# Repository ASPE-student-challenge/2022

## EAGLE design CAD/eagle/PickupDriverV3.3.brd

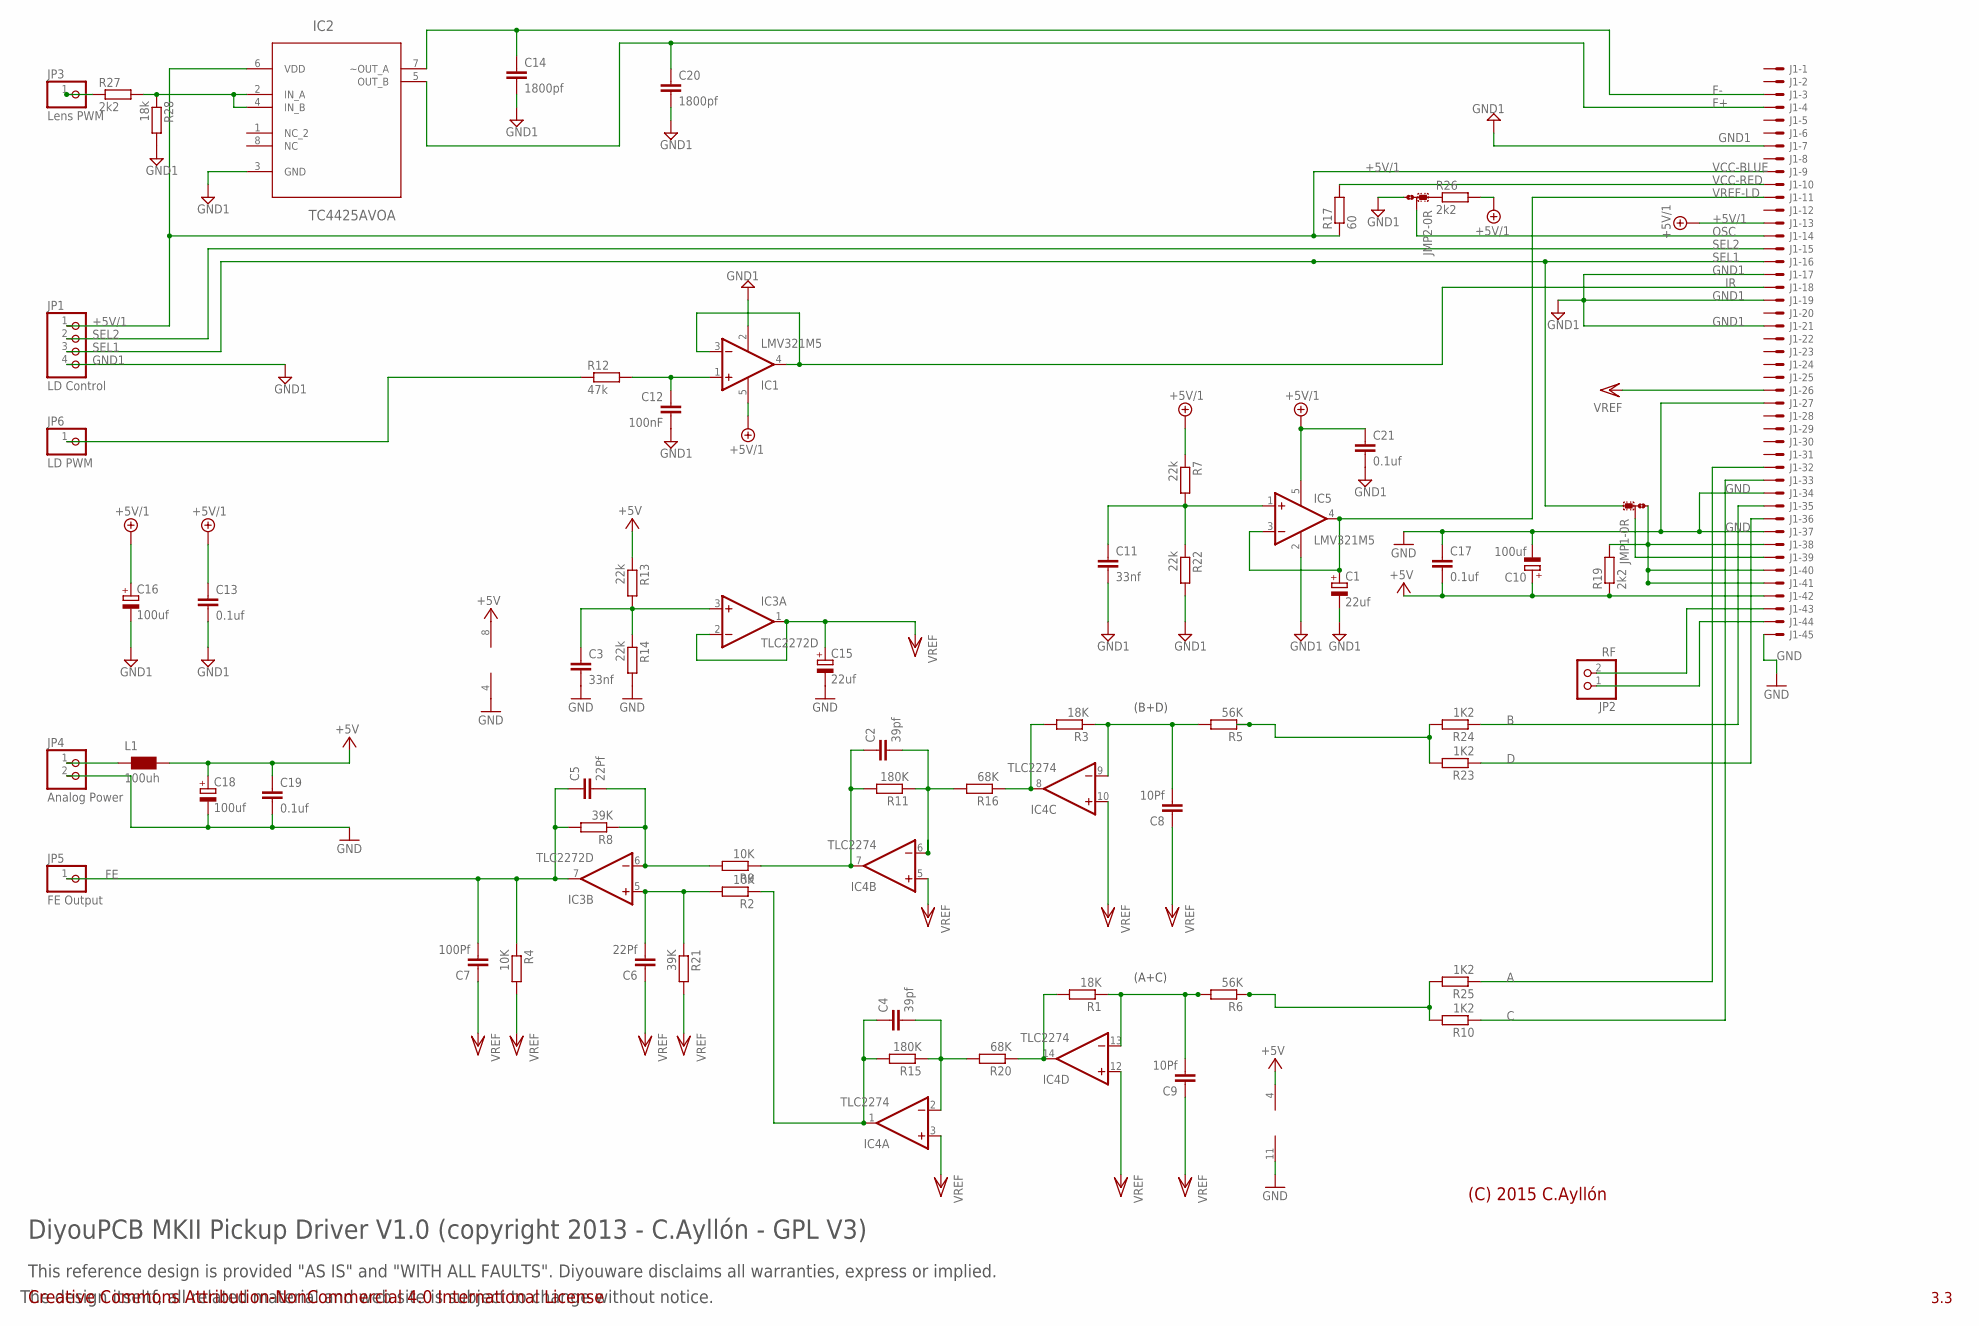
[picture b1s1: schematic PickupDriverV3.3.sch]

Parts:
C1, C15: 22uf; SMC_C
C2, C4: 39pf; C1206K
C3, C11: 33nf; C1206K
C5, C6: 22Pf; C1206K
C7: 100Pf; C1206K
C8, C9: 10Pf; C1206K
C10, C16, C18: 100uf; SMC_C
C12: 100nF; C1206K
C13, C17, C19, C21: 0.1uf; C1206K
C14, C20: 1800pf; C1206K
IC1, IC5: LMV321M5; SOT23-5
IC2: TC4425AVOA; SOIC127P600X175-8N
IC3: TLC2272D; SO08
IC4: TLC2274; SO14
J1: XF2H-4515-1LW
JMP1, JMP2: 0R-JUMPA; A0R-JMP
JP1: LD Control; 1X04
JP2: RF; 1X02
JP3: Lens PWM; 1X01
JP4: Analog Power; 1X02
JP5: FE Output; 1X01
JP6: LD PWM; 1X01
L1: 100uh; CHOKE-100UH-1
R1, R3: 18K; R1206
R2, R4, R9: 10K; R1206
R5, R6: 56K; R1206
R7, R13, R14, R22: 22k; R1206
R8, R21: 39K; R1206
R10, R23, R24, R25: 1K2; R1206
R11, R15: 180K; R1206
R12: 47k; R1206
R16, R20: 68K; R1206
R17: 60; R1206
R19, R26, R27: 2k2; R1206
R28: 18k; R1206

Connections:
+5V: C10.+, C17.2, C18.+, C19.1, IC3.8 (V+), IC4.4 (V+), J1.42 (MS), L1.2, R13.1, R19.1
+5V/1: C13.1, C16.+, C21.1, IC1.5 (V+), IC2.6 (VDD), IC5.5 (V+), J1.9 (MS), J1.13 (MS), JP1.1, R7.1, R17.1, R26.2
A: J1.32 (MS), R25.1
B: J1.35 (MS), R24.1
C: J1.33 (MS), R10.1
D: J1.36 (MS), R23.1
F+: C20.1, IC2.5 (OUT_B), J1.4 (MS)
F-: C14.1, IC2.7 (~OUT_A), J1.3 (MS)
FE: C5.1, C7.2, IC3.7 (OUT), JP5.1, R4.1, R8.2
FOCUS: IC2.2 (IN_A), IC2.4 (IN_B), R27.2, R28.1
GND: C3.2, C10.-, C15.-, C17.1, C18.-, C19.2, IC3.4 (V-), IC4.11 (V-), J1.27 (MS), J1.34 (MS), J1.37 (MS), J1.45 (MS), JP4.2, R14.2
GND1: C1.-, C11.2, C12.2, C13.2, C14.2, C16.-, C20.2, C21.2, IC1.2 (V-), IC2.3 (GND), IC5.2 (V-), J1.7 (MS), J1.17 (MS), J1.19 (MS), J1.21 (MS), JMP2.3, JP1.4, R22.2, R28.2
IR: IC1.3 (-IN), IC1.4 (OUT), J1.18 (MS)
LASER_CURR: JP6.1, R12.1
LENS: JP3.1, R27.1
unnamed: C11.1, IC5.1 (+IN), R7.2, R22.1
unnamed: C2.1, IC4.7 (OUT), R9.1, R11.2
unnamed: C12.1, IC1.1 (+IN), R12.2
unnamed: C8.2, IC4.9 (-IN), R3.1, R5.2
unnamed: IC4.14 (OUT), R1.2, R20.1
unnamed: C3.1, IC3.3 (+IN), R13.2, R14.1
unnamed: IC4.8 (OUT), R3.2, R16.1
unnamed: C9.2, IC4.13 (-IN), R1.1, R6.2
unnamed: C2.2, IC4.6 (-IN), R11.1, R16.2
unnamed: C5.2, IC3.6 (-IN), R8.1, R9.2
unnamed: C6.2, IC3.5 (+IN), R2.2, R21.1
unnamed: JP4.1, L1.1
unnamed: JMP2.1, R26.1
unnamed: C4.1, IC4.1 (OUT), R2.1, R15.2
unnamed: C4.2, IC4.2 (-IN), R15.1, R20.2
unnamed: R6.1, R10.2, R25.2
unnamed: J1.43 (MS), JP2.2
unnamed: J1.44 (MS), JP2.1
unnamed: R5.1, R23.2, R24.2
ND: J1.38 (MS), J1.40 (MS), J1.41 (MS), JMP1.3, R19.2
OSC: J1.14 (MS), JMP2.2
REDVCC: J1.10 (MS), R17.2
SEL1: J1.16 (MS), JMP1.1, JP1.3
SEL2: J1.15 (MS), JP1.2
SW: J1.39 (MS), JMP1.2
VREF: C6.1, C7.1, C8.1, C9.1, C15.+, IC3.1 (OUT), IC3.2 (-IN), IC4.3 (+IN), IC4.5 (+IN), IC4.10 (+IN), IC4.12 (+IN), J1.26 (MS), R4.2, R21.2
VREF-LD: C1.+, IC5.3 (-IN), IC5.4 (OUT), J1.11 (MS)

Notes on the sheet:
(B+D)
(A+C)
(C) 2015 C.Ayllón
DiyouPCB MKII Pickup Driver V1.0 (copyright 2013 - C.Ayllón - GPL V3)
Creative Commons Attribution-NonCommercial 4.0 International License
3.3
This reference design is provided "AS IS" and "WITH ALL FAULTS". Diyouware disclaims all warranties, express or implied.
The design itseltf, all related material and web site is subject to change without notice.
VCC-BLUE
VCC-RED

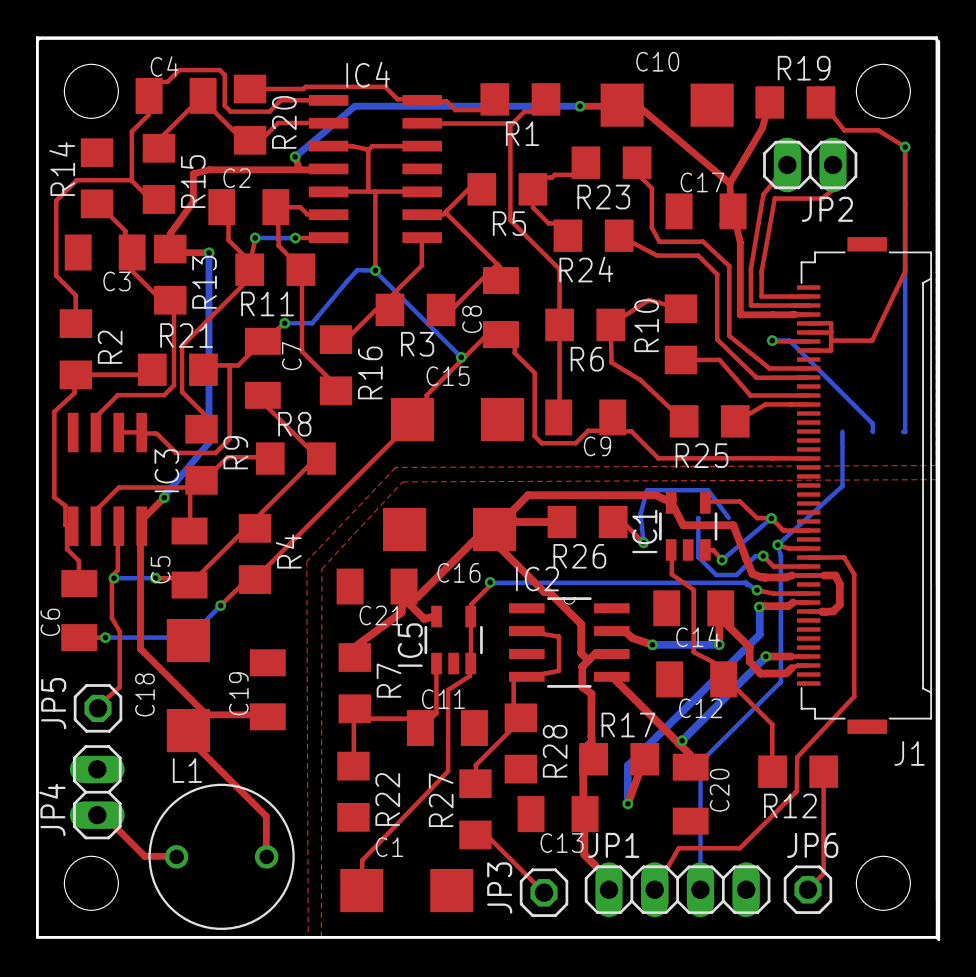
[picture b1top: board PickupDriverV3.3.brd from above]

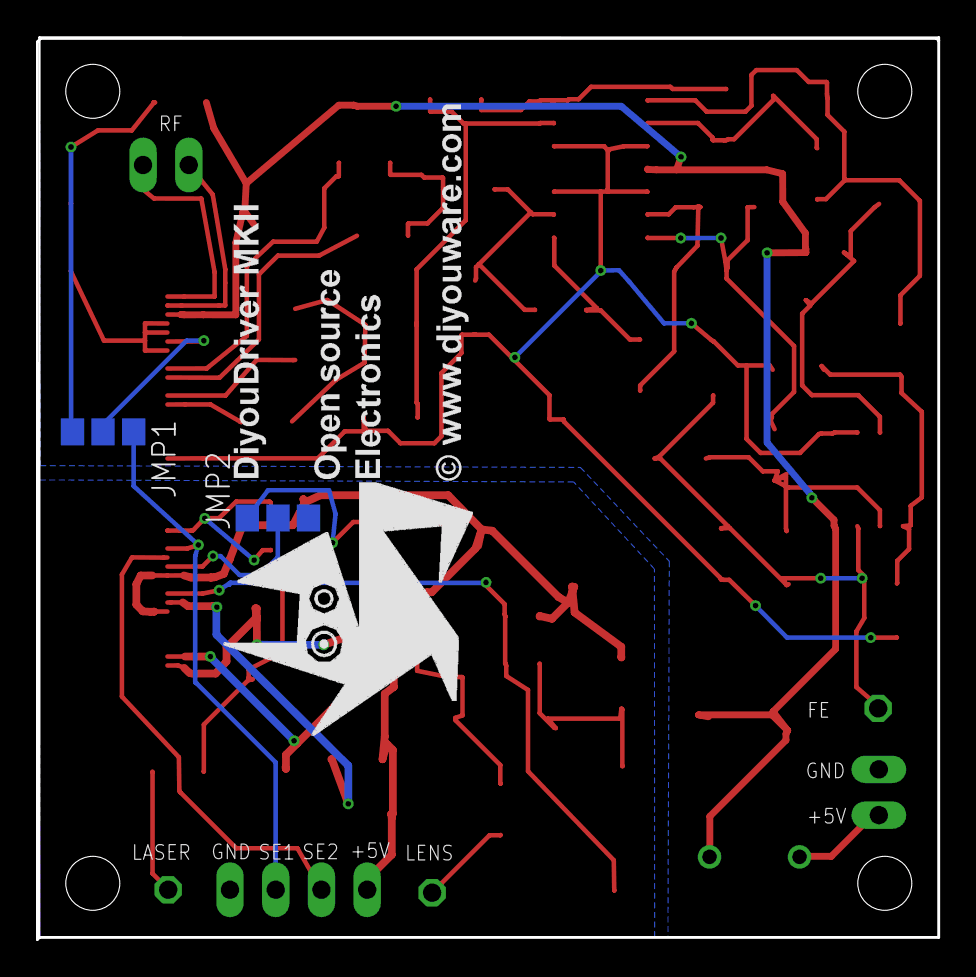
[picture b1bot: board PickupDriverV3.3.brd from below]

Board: 2 copper layers, 50.1 x 50.1 mm, 63 parts (2 on the bottom side), 42 nets.

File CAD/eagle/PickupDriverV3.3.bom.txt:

Partlist exported from C:/Users/MiUsuario/Documents/eagle/TwinTeeth/PickupDriverV3.3.sch at 06/11/2015 9:26:38

Assembly variant: 

Qty Value        Device        Parts             
1                XF2H-4515-1LW J1                
4   0.1uf        C-EUC1206K    C13, C17, C19, C21
2   0R-JUMPA     0R-JUMPA      JMP1, JMP2        
4   1K2          R-EU_R1206    R10, R23, R24, R25
3   2k2          R-EU_R1206    R19, R26, R27     
3   10K          R-EU_R1206    R2, R4, R9        
2   10Pf         C-EUC1206K    C8, C9            
2   18K          R-EU_R1206    R1, R3            
1   18k          R-EU_R1206    R28               
2   22Pf         C-EUC1206K    C5, C6            
4   22k          R-EU_R1206    R7, R13, R14, R22 
2   22uf         CPOL-EUSMCC   C1, C15           
2   33nf         C-EUC1206K    C3, C11           
2   39K          R-EU_R1206    R8, R21           
2   39pf         C-EUC1206K    C2, C4            
1   47k          R-EU_R1206    R12               
2   56K          R-EU_R1206    R5, R6            
1   60           R-EU_R1206    R17               
2   68K          R-EU_R1206    R16, R20          
1   100Pf        C-EUC1206K    C7                
1   100nF        C-EUC1206K    C12               
3   100uf        CPOL-EUSMCC   C10, C16, C18     
1   100uh        CHOKE-100UH   L1                
2   180K         R-EU_R1206    R11, R15          
2   1800pf       C-EUC1206K    C14, C20          
1   Analog Power PINHD-1X2     JP4               
1   FE Output    PINHD-1X1     JP5               
1   LD Control   PINHD-1X4     JP1               
1   LD PWM       PINHD-1X1     JP6               
2   LMV321M5     LMV321M5      IC1, IC5          
1   Lens PWM     PINHD-1X1     JP3               
1   RF           PINHD-1X2     JP2               
1   TC4425AVOA   TC4425AVOA    IC2               
1   TLC2272D     TLC2272D      IC3               
1   TLC2274      TLC274D       IC4

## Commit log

2022-01-30 CAD & documents folder
    CAD & documents folder
2022-02-01 PDIC used MLX75012
2022-02-02 Added opu mount files

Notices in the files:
parts and their libraries:
wurth_electronics_midcom_inc_v1-0: Copyright: Wurth Electronics Midcom, Inc.
